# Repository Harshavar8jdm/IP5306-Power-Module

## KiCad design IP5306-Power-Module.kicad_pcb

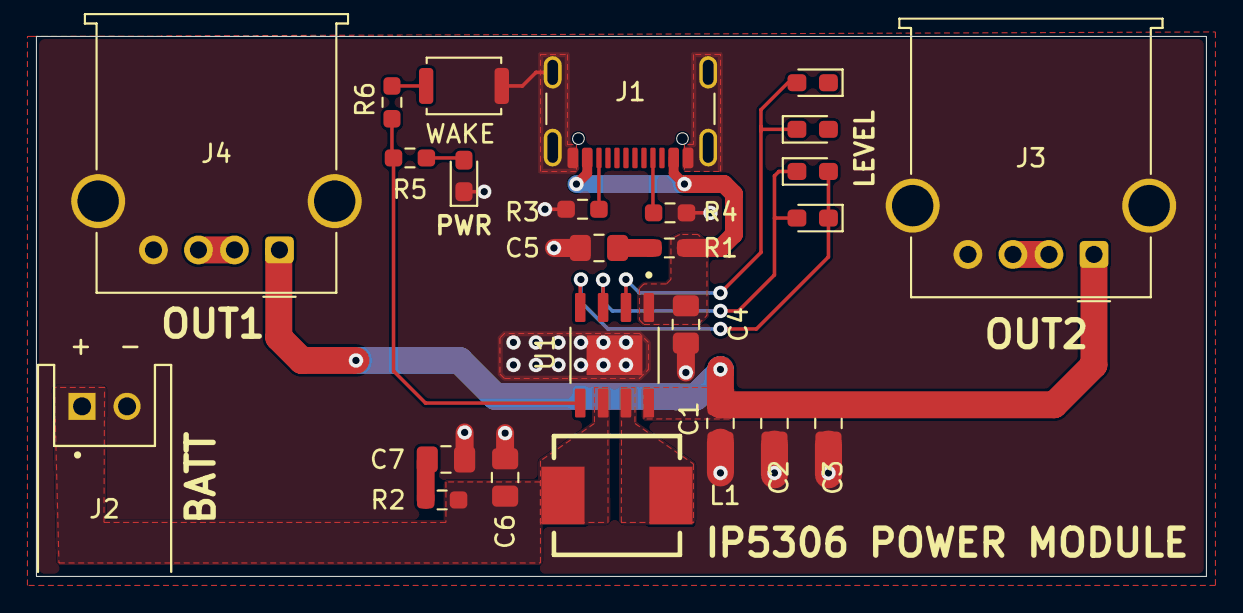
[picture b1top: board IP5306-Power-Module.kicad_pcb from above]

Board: 2 copper layers, 65.0 x 30.0 mm, 25 parts (0 on the bottom side), 17 nets.

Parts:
25%, 50%, 75%, 100%: LED; LED_0603_1608Metric_Pad1.05x0.95mm_HandSolder
C1, C2, C3: 22uF; C_0805_2012Metric_Pad1.18x1.45mm_HandSolder
C4, C5, C6, C7: 10uF; C_0805_2012Metric_Pad1.18x1.45mm_HandSolder
J1: USB_C_Receptacle_USB2.0_16P; USB_C_Receptacle_GCT_USB4105-xx-A_16P_TopMnt_Horizontal
J2: S2B-XH-A_LF__SN_; JST_S2B-XH-A_LF__SN_
J3, J4: USB_A; USB_A_Molex_67643_Horizontal
L1: L; IND-SMD_L7_0-W6_6_SPM70701R0MESL_C5332207
LEVEL: KEY; SW_Push_SPST_NO_Alps_SKRK
PWR: LED; LED_0603_1608Metric_Pad1.05x0.95mm_HandSolder
R1, R2: 2R; R_0603_1608Metric_Pad0.98x0.95mm_HandSolder
R3, R4: 5.1K; R_0603_1608Metric_Pad0.98x0.95mm_HandSolder
R5: 20R; R_0603_1608Metric_Pad0.98x0.95mm_HandSolder
R6: 10K; R_0603_1608Metric_Pad0.98x0.95mm_HandSolder
U1: IP5306; SOP127P600X165-9N

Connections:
/BAT: C6.1, J2.1, L1.2, R2.1, U1.6 (BAT)
/CC1: J1.A5 (CC1), R4.1
/CC2: J1.B5 (CC2), R3.1
/KEY: R5.1, R6.1, U1.5 (KEY)
/LED1: 25%.2 (A), 50%.1 (K), U1.2 (LED1)
/LED2: 75%.1 (K), 100%.2 (A), U1.3 (LED2)
/LED3: 25%.1 (K), 50%.2 (A), 75%.2 (A), 100%.1 (K), U1.4 (LED3)
/SW: L1.1, U1.7 (SW)
/VIN: C4.1, J1.A4 (VBUS), J1.A9 (VBUS), J1.B4 (VBUS), J1.B9 (VBUS), R1.1, U1.1 (VIN)
/VOUT: C1.1, C2.1, C3.1, J3.1 (VBUS), J4.1 (VBUS), U1.8 (VOUT)
GND: C1.2, C2.2, C3.2, C4.2, C5.2, C6.2, C7.2, J1.A1 (GND), J1.A12 (GND), J1.B1 (GND), J1.B12 (GND), J1.SH (SHIELD), J2.2, J3.4 (GND), J3.SH (Shield), J4.4 (GND), J4.SH (Shield), LEVEL.2, PWR.1 (K), R3.2, R4.2, U1.9 (POWERPAD)
unnamed: C5.1, R1.2
unnamed: C7.1, R2.2
unnamed: PWR.2 (A), R5.2
unnamed: J3.2 (D-), J3.3 (D+)
unnamed: J4.2 (D-), J4.3 (D+)
unnamed: LEVEL.1, R6.2
